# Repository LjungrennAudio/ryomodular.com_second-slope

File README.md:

# ryomodular.com_second-slope
 a peak/trough-analog min/median/max module...

2408310019

this is a slightly interesting one - clearly this started as two separate module and then got cobbled together into abit of a monster but i suspect its got more legs yet and could really turn into something even more original and special.

it seems to consist of a min/median/max module - asolute classic analog logic tool a nd stalwart feature of any good patch programmable system - but nailed on the end is a peak/trough detector with a noice feature set of rising/falling/steady/moving outs.
it's definitely got legs as something but i'd like to find a away to make it far more unique and intersting than just plain old analog logic basics as is.
it's yet another candidate wth high possibilities as part of the jacob's ladder projecgt but i don't know if there's room fo all the functionality this offers in such a mdoule as that.

we'll have to watch and wait with baited breath, eh?

#######

2409060303

see jacob's ladder for continuation.

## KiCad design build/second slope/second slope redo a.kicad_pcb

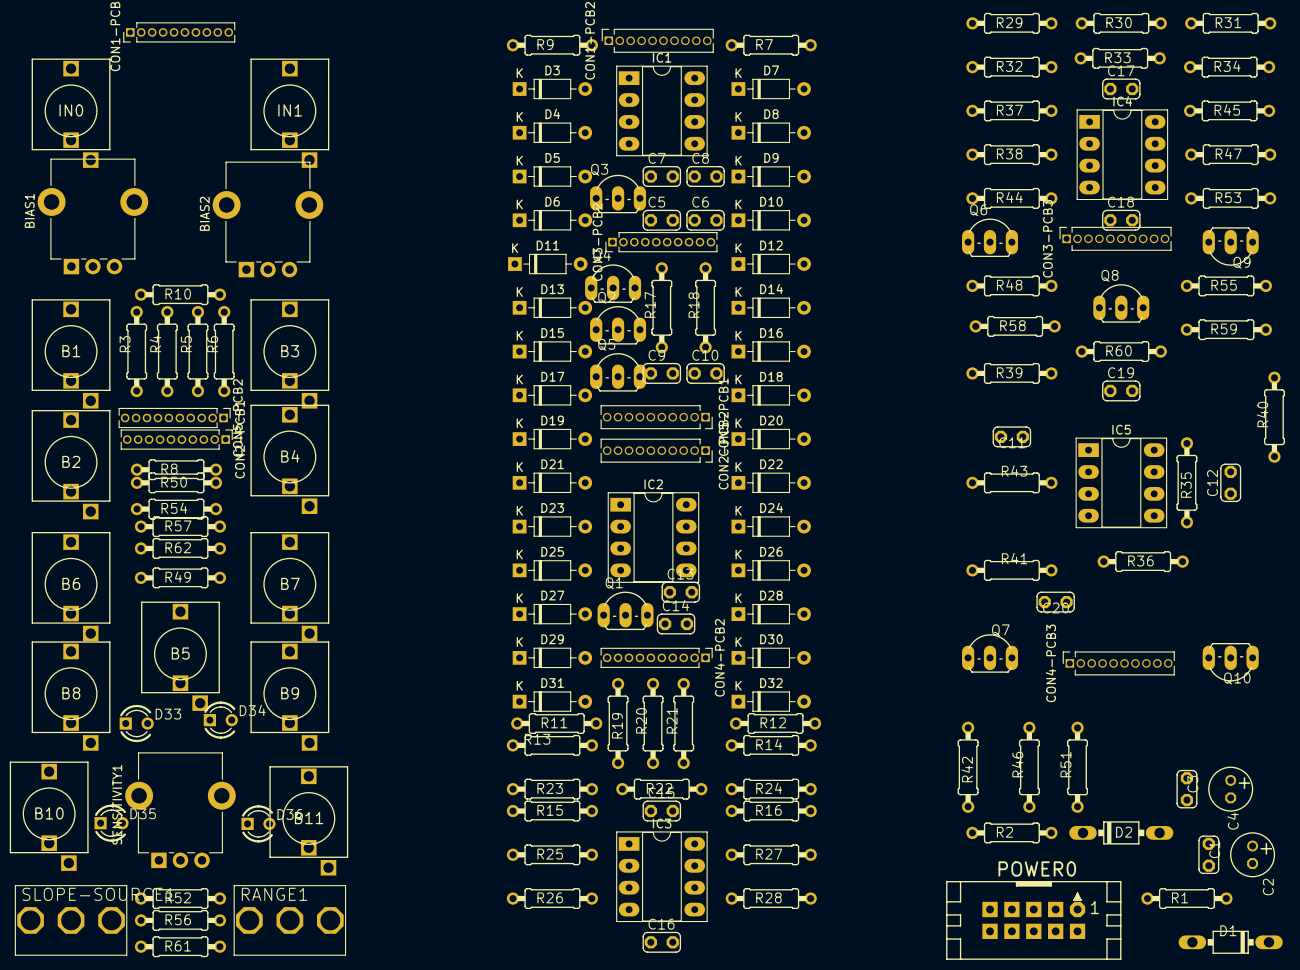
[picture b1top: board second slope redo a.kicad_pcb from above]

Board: 2 copper layers, 162 parts (0 on the bottom side), 97 nets, no tracks yet.

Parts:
B1: in 3; THONKICON-TWISTED
B2: max out; THONKICON-TWISTED
B3: in 4; THONKICON-TWISTED
B4: min out; THONKICON-TWISTED
B5: ext in; THONKICON-TWISTED
B6: high out 1; THONKICON-TWISTED
B7: high out 2; THONKICON-TWISTED
B8: rising out; THONKICON-TWISTED
B9: falling out; THONKICON-TWISTED
B10: steady out; THONKICON-TWISTED
B11: rising&falling out; THONKICON-TWISTED
BIAS1, BIAS2: 100K; Potentiometer_Alpha_RD901F-40-00D_Single_Vertical_CircularH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
C1, C3, C7, C8, C11, C12, C13, C14, C15, C16, C17, C18, C19, C20: 100nF; C025-024X044
C2, C4: 10uF; E2-5
C5, C6, C9, C10: 68pF; C025-024X044
CON1-PCB1, CON2-PCB1, CON3-PCB2, CON4-PCB2, CON5-PCB2: MA10-1; PinHeader_1x10_P1.27mm_Vertical
CON1-PCB2, CON2-PCB2, CON3-PCB3, CON4-PCB3, CON5-PCB1: MA10-1; PinSocket_1x10_P1.27mm_Vertical
D1, D2: SB130; DO41-7
D3, D4, D5, D6, D7, D8, D9, D10, D11, D12, D13, D14, D15, D16, D17, D18, D19, D20, D21, D22, D23, D24, D25, D26, D27, D28, D29, D30, D31, D32: 1N4148; D_DO-35_SOD27_P7.62mm_Horizontal
D33, D34, D35, D36: CQY99; LED3MM
IC1, IC2, IC3: MC4558; DIP-8_W7.62mm_Socket_LongPads
IC4, IC5: TL072; DIP-8_W7.62mm_Socket_LongPads
IN0: in 1; THONKICON-TWISTED
IN1: inn 2; THONKICON-TWISTED
POWER0: CON10L
Q1, Q6, Q7, Q9, Q10: BC557; TO92-LINE
Q2, Q3, Q4, Q5, Q8: BC547; TO92-LINE
R1, R2: 10R; 0207_9
R3, R4, R5, R6: 24K; 0207_9
R7, R8, R9, R10, R11, R12, R14, R17, R18, R19, R20, R25, R26, R29, R35, R36: 100K; 0207_9
R13, R16, R27, R28: 330; 0207_9
R15, R21, R22, R23, R24, R49, R50, R52, R54, R56, R57, R61, R62: 1K; 0207_9
R30, R32, R38, R39, R40, R41: 4.7K; 0207_9
R31, R37, R42, R43, R45, R58: 10K; 0207_9
R33, R34: 1M; 0207_9
R44, R46, R59: 3.3K; 0207_9
R47: 47K; 0207_9
R48, R51, R55, R60: 1.8K; 0207_9
R53: 2.2K; 0207_9
RANGE1: SW_SPST; SPDT-HORIZONTAL-TOP-SUBMINI-MULTICOMP
SENSITIVITY1: 1M; Potentiometer_Alpha_RD901F-40-00D_Single_Vertical_CircularH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
SLOPE-SOURCE1: SW_DP3T; SPDT-HORIZONTAL-TOP-SUBMINI-MULTICOMP

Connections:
0V: B1.TIP, B3.TIP, C1.2, C2.-, C3.1, C4.+, C7.2, C8.1, C11.2, C12.2, C13.2, C14.1, C15.2, C16.1, C17.2, C18.1, C19.2, C20.1, CON1-PCB1.2, CON1-PCB1.10, CON1-PCB2.2, CON1-PCB2.10, CON2-PCB1.2, CON3-PCB2.2, CON3-PCB2.10, CON3-PCB3.2, CON3-PCB3.10, CON4-PCB3.2, CON5-PCB1.2, CON5-PCB1.10, CON5-PCB2.2, CON5-PCB2.10, D32.2 (A), POWER0.3, POWER0.4, POWER0.5, POWER0.6, POWER0.7, POWER0.8, Q8.3 (E), R29.1, R43.2, R49.2, R52.2, R56.2, R61.2
+12V: C1.1, C2.+, C7.1, C13.1, C15.1, C17.1, C19.1, CON1-PCB1.3, CON1-PCB2.3, CON2-PCB1.3, CON3-PCB2.3, CON3-PCB3.3, CON4-PCB3.3, CON5-PCB1.3, CON5-PCB2.3, D1.C, D11.2 (A), IC1.4 (V+), IC2.4 (V+), IC3.4 (V+), IC4.4 (V+), IC5.4 (V+), Q6.3 (E), Q7.3 (E), Q9.3 (E), Q10.3 (E), R3.1, R5.1, R9.1, R15.1, R17.1, R18.1, R19.1, R20.1, R34.1, R37.2, R42.2, R45.2, R58.2
-12V: C3.2, C4.-, C8.2, C14.2, C16.2, C18.2, C20.2, CON1-PCB1.1, CON1-PCB2.1, CON2-PCB1.1, CON3-PCB2.1, CON3-PCB3.1, CON4-PCB3.1, CON5-PCB1.1, CON5-PCB2.1, D2.A, D28.2 (A), D29.2 (A), D30.2 (A), D31.2 (A), R4.1, R6.1, R7.2, R14.1, R21.1, R22.1, R23.1, R24.1, R33.2
/FALLING: CON4-PCB3.5, R54.2
/FALLING-OUT: B9.TIP, CON2-PCB1.5
/HIGH OUT 1: R25.2, R27.2, SLOPE-SOURCE1.2
/HIGH OUT 2: R26.2, R28.2
/HIGH-OUT1: B6.TIP, CON2-PCB1.9
/HIGH-OUT2: B7.TIP, CON2-PCB1.8
/IN-1: CON1-PCB1.9, D3.2 (A), D4.1 (K), IC2.3 (+IN)
/IN-2: CON1-PCB1.8, D5.2 (A), D6.1 (K), IC2.5 (+IN)
/IN-3: CON1-PCB1.7, D7.2 (A), D8.1 (K), IC3.3 (+IN)
/LED1: CON3-PCB2.7, R44.2
/LED2: CON3-PCB2.6, R53.2
/LED3: CON3-PCB2.5, R59.2
/LED4: CON3-PCB2.4, R46.2
/LED-1: CON3-PCB3.7, CON5-PCB2.7
/LED-2: CON3-PCB3.6, CON5-PCB2.6
/LED-3: CON3-PCB3.5, CON5-PCB2.5
/LED-4: CON3-PCB3.4, CON5-PCB2.4
/MAX OUT: CON1-PCB2.5, R11.2, R13.2
/MAX-OUT: B2.TIP, CON1-PCB1.5
/MIN OUT: CON1-PCB2.4, R12.2, R16.2, SLOPE-SOURCE1.1
/MIN-OUT: B4.TIP, CON1-PCB1.4
/RISING: CON4-PCB3.6, R50.2
/RISING&FALLING: CON4-PCB3.10, R62.2
/RISING&FALLING-OUT: B11.TIP, CON2-PCB1.10
/RISING-OUT: B8.TIP, CON2-PCB1.6
/SIGNAL IN: CON4-PCB3.7, R29.2, R30.1, R31.1, R32.1
/STEADY: CON4-PCB3.4, R57.2
/STEADY-OUT: B10.TIP, CON2-PCB1.4
unnamed: B5.TIP, SLOPE-SOURCE1.3
unnamed: C5.1, IC1.1 (OUT), R13.1
unnamed: C5.2, IC1.2 (-IN), R11.1
unnamed: C6.1, IC1.7 (OUT), R16.1
unnamed: C6.2, IC1.6 (-IN), R12.1
unnamed: C9.1, IC4.1 (OUT), R27.1
unnamed: C9.2, IC4.2 (-IN), R25.1
unnamed: C10.1, IC4.7 (OUT), R28.1
unnamed: C10.2, IC4.6 (-IN), R26.1
unnamed: C12.1, RANGE1.2 (B)
unnamed: CON2-PCB2.1, CON4-PCB2.1
unnamed: CON2-PCB2.2, CON4-PCB2.2
unnamed: CON2-PCB2.3, CON4-PCB2.3
unnamed: CON2-PCB2.4, CON4-PCB2.4
unnamed: CON2-PCB2.5, CON4-PCB2.5
unnamed: CON2-PCB2.6, CON4-PCB2.6
unnamed: CON2-PCB2.7, CON4-PCB2.7
unnamed: CON2-PCB2.8, CON4-PCB2.8
unnamed: CON2-PCB2.9, CON4-PCB2.9
unnamed: D1.A, R1.2
unnamed: D2.C, R2.2
unnamed: D3.1 (K), D5.1 (K), D7.1 (K), D9.1 (K), R9.2, R10.1
unnamed: D9.2 (A), D10.1 (K), IC3.5 (+IN)
unnamed: D4.2 (A), D6.2 (A), D8.2 (A), D10.2 (A), R7.1, R8.1
unnamed: D11.1 (K), Q1.2 (B), R14.2
unnamed: D12.1 (K), D13.1 (K), D14.1 (K), D15.1 (K), Q3.3 (E)
unnamed: D12.2 (A), D13.2 (A), D14.2 (A), D16.2 (A), D17.2 (A), D21.2 (A), D25.2 (A), D26.2 (A), IC2.1 (OUT), IC2.7 (OUT), IC3.7 (OUT)
unnamed: D15.2 (A), D18.2 (A), D23.2 (A), D27.2 (A), IC2.2 (-IN), IC2.6 (-IN), IC3.2 (-IN), IC3.6 (-IN), IC4.3 (+IN), IC4.5 (+IN), Q1.1 (C)
unnamed: D16.1 (K), D17.1 (K), D18.1 (K), D19.1 (K), Q4.3 (E)
unnamed: D19.2 (A), D22.2 (A), IC3.1 (OUT)
unnamed: D20.1 (K), D22.1 (K), D23.1 (K)
unnamed: D20.2 (A), D24.2 (A)
unnamed: D21.1 (K), Q2.3 (E)
unnamed: D24.1 (K), D25.1 (K), D26.1 (K), D27.1 (K), Q5.3 (E)
unnamed: D28.1 (K), Q2.2 (B), R17.2
unnamed: D29.1 (K), Q3.2 (B), R18.2
unnamed: D30.1 (K), Q4.2 (B), R19.2
unnamed: D31.1 (K), Q5.2 (B), R20.2
unnamed: D32.1 (K), Q8.2 (B), R35.1, R36.2, R43.1
unnamed: IC1.3 (+IN), R8.2
unnamed: IC1.5 (+IN), R10.2
unnamed: IC5.1 (OUT), R35.2, R38.1, R39.1
unnamed: IC5.2 (-IN), R30.2, R33.1
unnamed: IC5.3 (+IN), IC5.6 (-IN), RANGE1.1 (A)
unnamed: IC5.5 (+IN), R32.2, R34.2
unnamed: IC5.7 (OUT), R36.1, R40.1, R41.1
unnamed: POWER0.1, POWER0.2, R2.1
unnamed: POWER0.9, POWER0.10, R1.1
unnamed: Q1.3 (E), R15.2
unnamed: Q2.1 (C), R21.2
unnamed: Q3.1 (C), R22.2
unnamed: Q4.1 (C), R23.2
unnamed: Q5.1 (C), R24.2
unnamed: Q6.1 (C), R44.1, R48.1
unnamed: Q6.2 (B), R37.1, R38.2
unnamed: Q7.1 (C), R46.1, R51.1
unnamed: Q7.2 (B), R41.2, R42.1
unnamed: Q8.1 (C), R47.2
unnamed: Q9.1 (C), R53.1, R55.1
unnamed: Q9.2 (B), R45.1, R47.1
unnamed: Q10.1 (C), R59.1, R60.1
unnamed: Q10.2 (B), R39.2, R40.2, R58.1
unnamed: R48.2, R49.1, R50.1
unnamed: R51.2, R52.1, R54.1
unnamed: R55.2, R56.1, R57.1
unnamed: R60.2, R61.1, R62.1

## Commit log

2024-08-30 init commit of second slope...
    yup, it's another module unlikely to ever be published or released in the state it's seen here! btu this is such wonderful analogue logic goodness it's absolutely sure to find light _somewhere_
2024-08-31 further init files added
    yup, moar!
2025-01-13 filing
